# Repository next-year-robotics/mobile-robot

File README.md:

# Mobile Robot

Maknae (Mobile Assistant for Kin's Needs And Errands) is a small mobile robot for older adults who have trouble getting around. The goal is a robot that brings things like a water bottle or glasses at home, walks along with the person outside, and lets family know when something goes wrong.

This repository has the robot itself: the frame CAD and base interface board, the STM32 firmware, and the ROS 2 packages on the Raspberry Pi 5. The phone app and the caregiver dashboard live in their own repositories (see [Related repositories](#related-repositories)).

The base, odometry, person following, the SO-101 arm, the phone link and caregiver telemetry all run on the real robot. LiDAR mapping was added recently, and navigation comes next.

## What it does

- Follows a person carrying an ArUco marker at about 1.1 m, at up to 0.25 m/s, and stops when the marker is lost.
- Picks up objects and hands them over with an SO-101 arm on the top plate.
- Can be driven with a gamepad at any time; `twist_mux` gives it priority over the follower.
- Fuses wheel odometry with the IMU gyro in a `robot_localization` EKF.
- Builds 2D maps with an RPLIDAR C1 and `slam_toolbox`.
- Talks to the phone app over WebSocket: pick a destination, start and stop the trip, and answer SOS requests with the phone's location.
- Sends status, events and SOS to Firebase so a caregiver can watch from the web dashboard and get push notifications.

## Hardware

| Part | Used here |
| --- | --- |
| Frame | Aluminium extrusion, 450 × 400 × 368 mm, 9.8 kg measured |
| Drive | 2 × JGB37-520 DC gear motor with hall encoder, 100 mm wheels, 264 mm track, casters |
| Motor driver | Cytron MDD3A |
| Microcontroller | STM32F446RE (NUCLEO-F446RE), FreeRTOS and micro-ROS |
| Computer | Raspberry Pi 5, Ubuntu 24.04, ROS 2 Jazzy |
| Arm | SO-101 with gripper, USB to the Pi |
| Sensors | Logitech C920 camera, ICM-42688-P IMU (on the MCU, SPI), RPLIDAR C1 |
| Power | 4S LiFePO4 battery with reverse-polarity diode |

The MCU and the Pi are wired directly, STM32 USART1 to Pi UART0 at 921600 baud, and micro-ROS runs over that link. The MCU closes the wheel speed loops and publishes encoders and IMU at 100 Hz. The firmware caps wheel speed at 0.76 m/s; the follow controller stays well below that.

<table>
  <tr>
    <td></td>
    <td></td>
    <td></td>
    <td></td>
  </tr>
  <tr>
    <td align="center">Frame CAD</td>
    <td align="center">Frame</td>
    <td align="center">Base interface board</td>
    <td align="center">Wiring</td>
  </tr>
</table>

## How it fits together

```mermaid
flowchart LR
  APP[Phone app] <-->|WebSocket| BRIDGE
  subgraph PI5["Raspberry Pi 5 (ROS 2 Jazzy)"]
    BRIDGE[mr_phone_bridge] <--> MISSION[mr_mission]
    MISSION --> FOLLOW[follow]
    CAM[C920 camera] --> ARUCO[aruco_opencv] --> TRACK[marker tracker] --> FOLLOW
    FOLLOW --> MUX[twist_mux]
    JOY[Gamepad] --> MUX
    ODOM[mr_base wheel odometry] --> EKF[EKF]
    LIDAR[RPLIDAR C1] --> SLAM[slam_toolbox]
    MISSION --> TELE[mr_care_telemetry]
    ARMCTL[Arm control]
  end
  subgraph MCU["STM32F446RE (FreeRTOS, micro-ROS)"]
    CTRL[Wheel speed control]
    IMU[ICM-42688-P]
  end
  MUX -->|cmd_vel| CTRL
  CTRL -->|encoder ticks| ODOM
  IMU -->|gyro| EKF
  TELE --> RTDB[(Firebase RTDB)] --> DASH[Caregiver dashboard]
  ARMCTL -->|USB| ARM[SO-101 arm]
```

## Repository layout

```text
hardware/mobile_base/      frame CAD (STEP) and measured robot geometry
hardware/base_interface/   KiCad perfboard for the MCU, motor driver, IMU and power
firmware/base_controller/  STM32CubeMX project with FreeRTOS and micro-ROS
software/ros_pkgs/         ROS 2 packages
software/contracts/        JSON schemas shared with the phone app and the dashboard
software/patches/          patches for upstream ROS packages
```

| Package | Purpose |
| --- | --- |
| `mr_description` | URDF from measured geometry, meshes, RViz config |
| `mr_base` | wheel odometry, `odom` to `base_footprint` TF, IMU covariance |
| `mr_bringup` | launch files and config for camera, teleop, `twist_mux`, EKF, LiDAR, SLAM |
| `mr_aruco` | marker tracking filter, person following, alignment to fixed markers |
| `mr_mission` | trip state for the app, turns following on and off, battery estimate |
| `mr_phone_bridge` | WebSocket gateway for the phone app, plus a mock that runs without ROS |
| `mr_care_telemetry` | writes status and events to Firebase RTDB, with an offline queue |
| `mr_msgs`, `mr_aruco_msgs`, `mr_care_msgs` | messages and actions |

## Getting started

### Firmware

The firmware is a CMake project generated by STM32CubeMX. Build the micro-ROS static library once (it runs in Docker), then build and flash with an ST-Link.

```bash
cd firmware/base_controller
./micro_ros/build_libmicroros.sh
cmake --preset Release
cmake --build --preset Release
arm-none-eabi-objcopy -O binary build/Release/base_controller.elf build/Release/base_controller.bin
st-flash --reset write build/Release/base_controller.bin 0x08000000
```

### ROS 2 workspace on the Pi

```bash
mkdir -p ~/ros2_ws/src && cd ~/ros2_ws/src
git clone https://github.com/next-year-robotics/mobile-robot.git
cd ~/ros2_ws
rosdep install --from-paths src --ignore-src -y
colcon build --symlink-install
source install/setup.bash
```

The launch files start `micro_ros_agent` on `/dev/ttyAMA0` from a separate workspace, `~/microros_ws`; build it there following the micro-ROS setup guide. usb_cam 0.8.1 from apt stamps camera frames up to a second in the past, which makes the follower drop every sample. Build usb_cam from source in the same workspace with `software/patches/usb_cam-0.8.1-epoch-time-shift.patch` applied.

### Run

```bash
ros2 launch mr_bringup teleop.launch.py    # drive with the gamepad (hold LB or RB)
ros2 launch mr_bringup follow.launch.py    # follow the marker
ros2 launch mr_bringup slam.launch.py      # drive around slowly and build a map
```

## Roadmap

- Measure the LiDAR mount and tune SLAM
- Nav2 for going to saved places
- Simulation

## Related repositories

- [senior-care-android](https://github.com/next-year-robotics/senior-care-android): phone app for the person going out with the robot
- [senior-care-dashboard](https://github.com/next-year-robotics/senior-care-dashboard): web dashboard for caregivers
- [mobile-robot-booth](https://github.com/next-year-robotics/mobile-robot-booth): live dashboard and avatar used for demos

## License

- `software/` and `firmware/`: [Apache-2.0](LICENSES/Apache-2.0.txt)
- `hardware/`: [CERN-OHL-P-2.0](LICENSES/CERN-OHL-P-2.0.txt)
- Documentation and photos: [CC BY 4.0](LICENSES/CC-BY-4.0.txt)

Third-party code such as the ST HAL, CMSIS and FreeRTOS keeps its own license. See [LICENSE.md](LICENSE.md).

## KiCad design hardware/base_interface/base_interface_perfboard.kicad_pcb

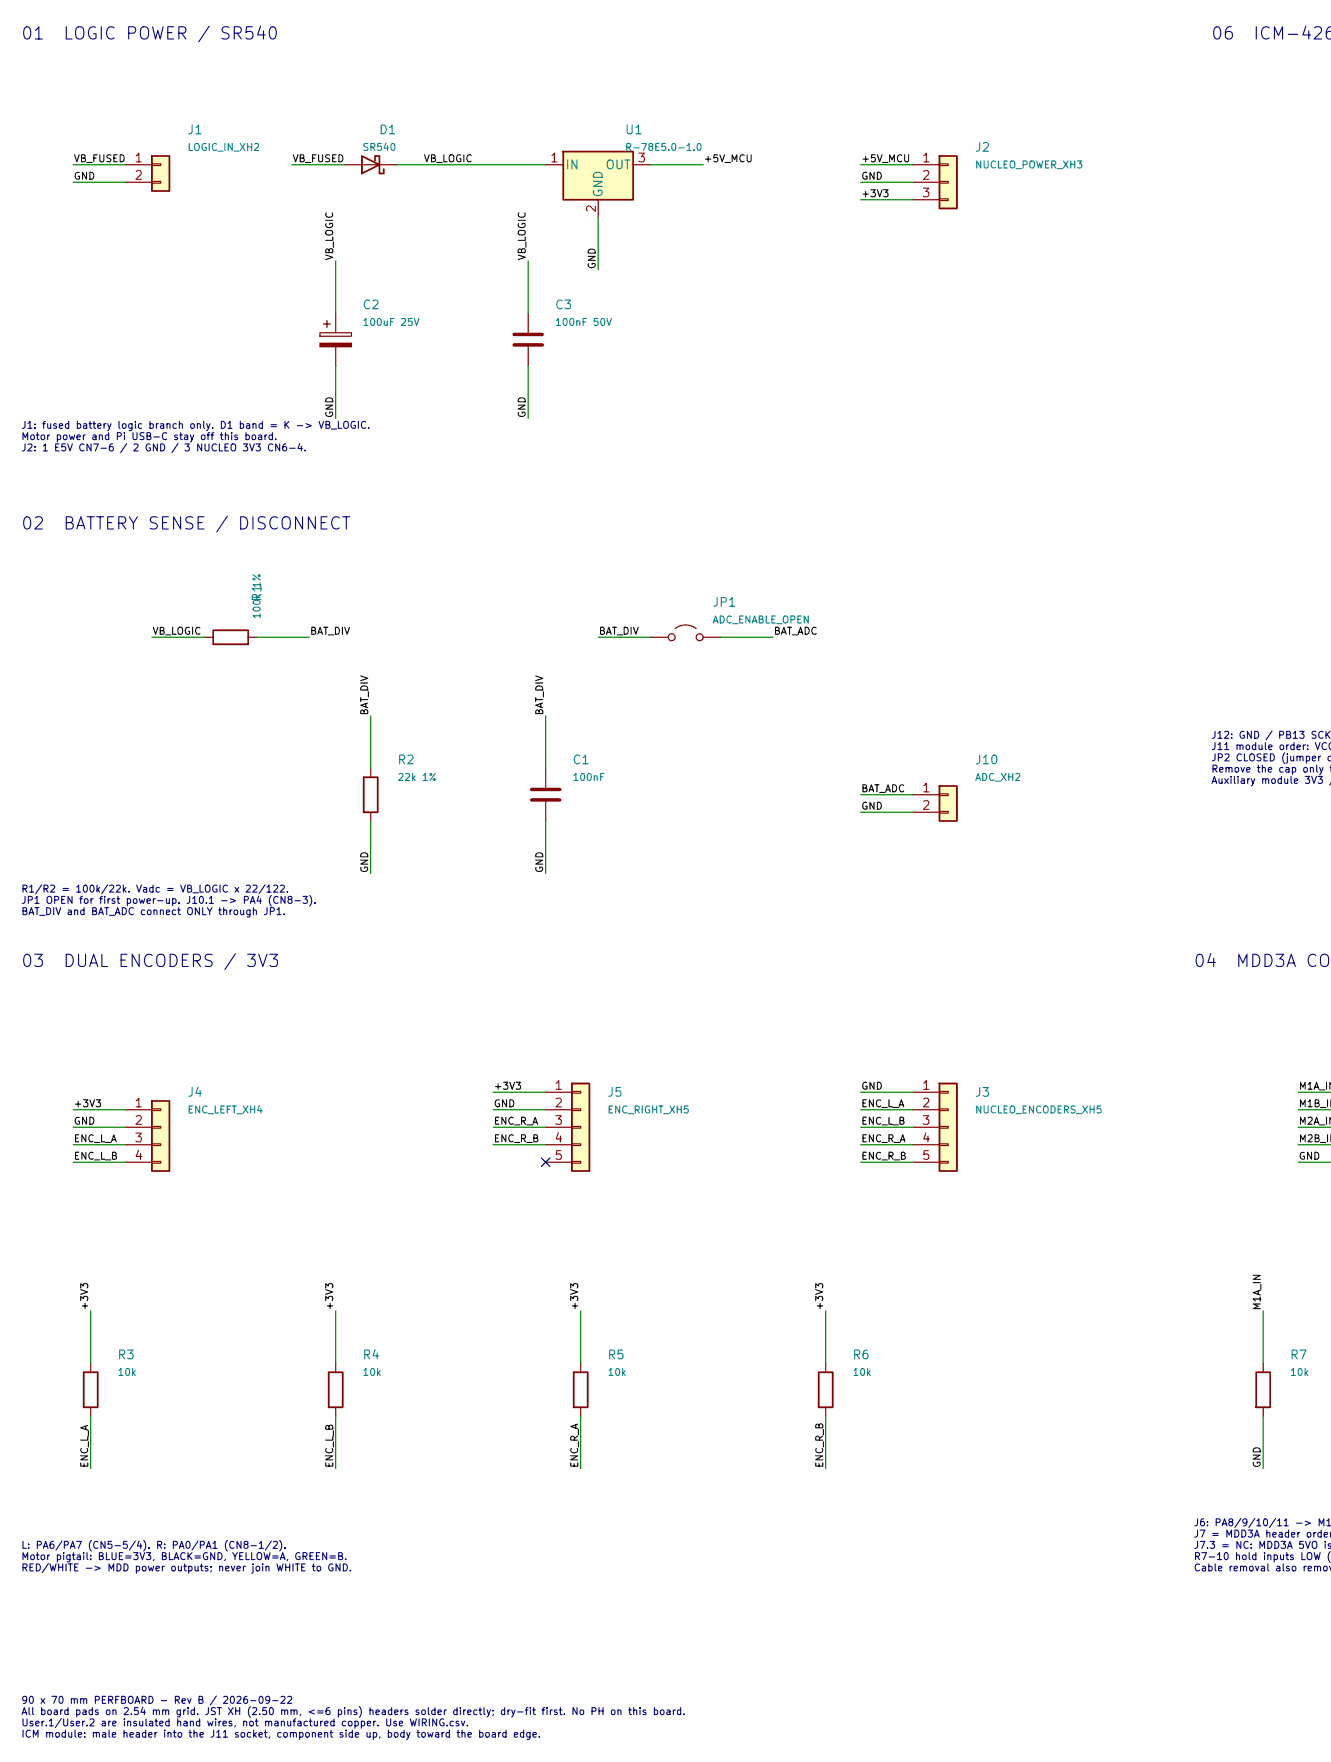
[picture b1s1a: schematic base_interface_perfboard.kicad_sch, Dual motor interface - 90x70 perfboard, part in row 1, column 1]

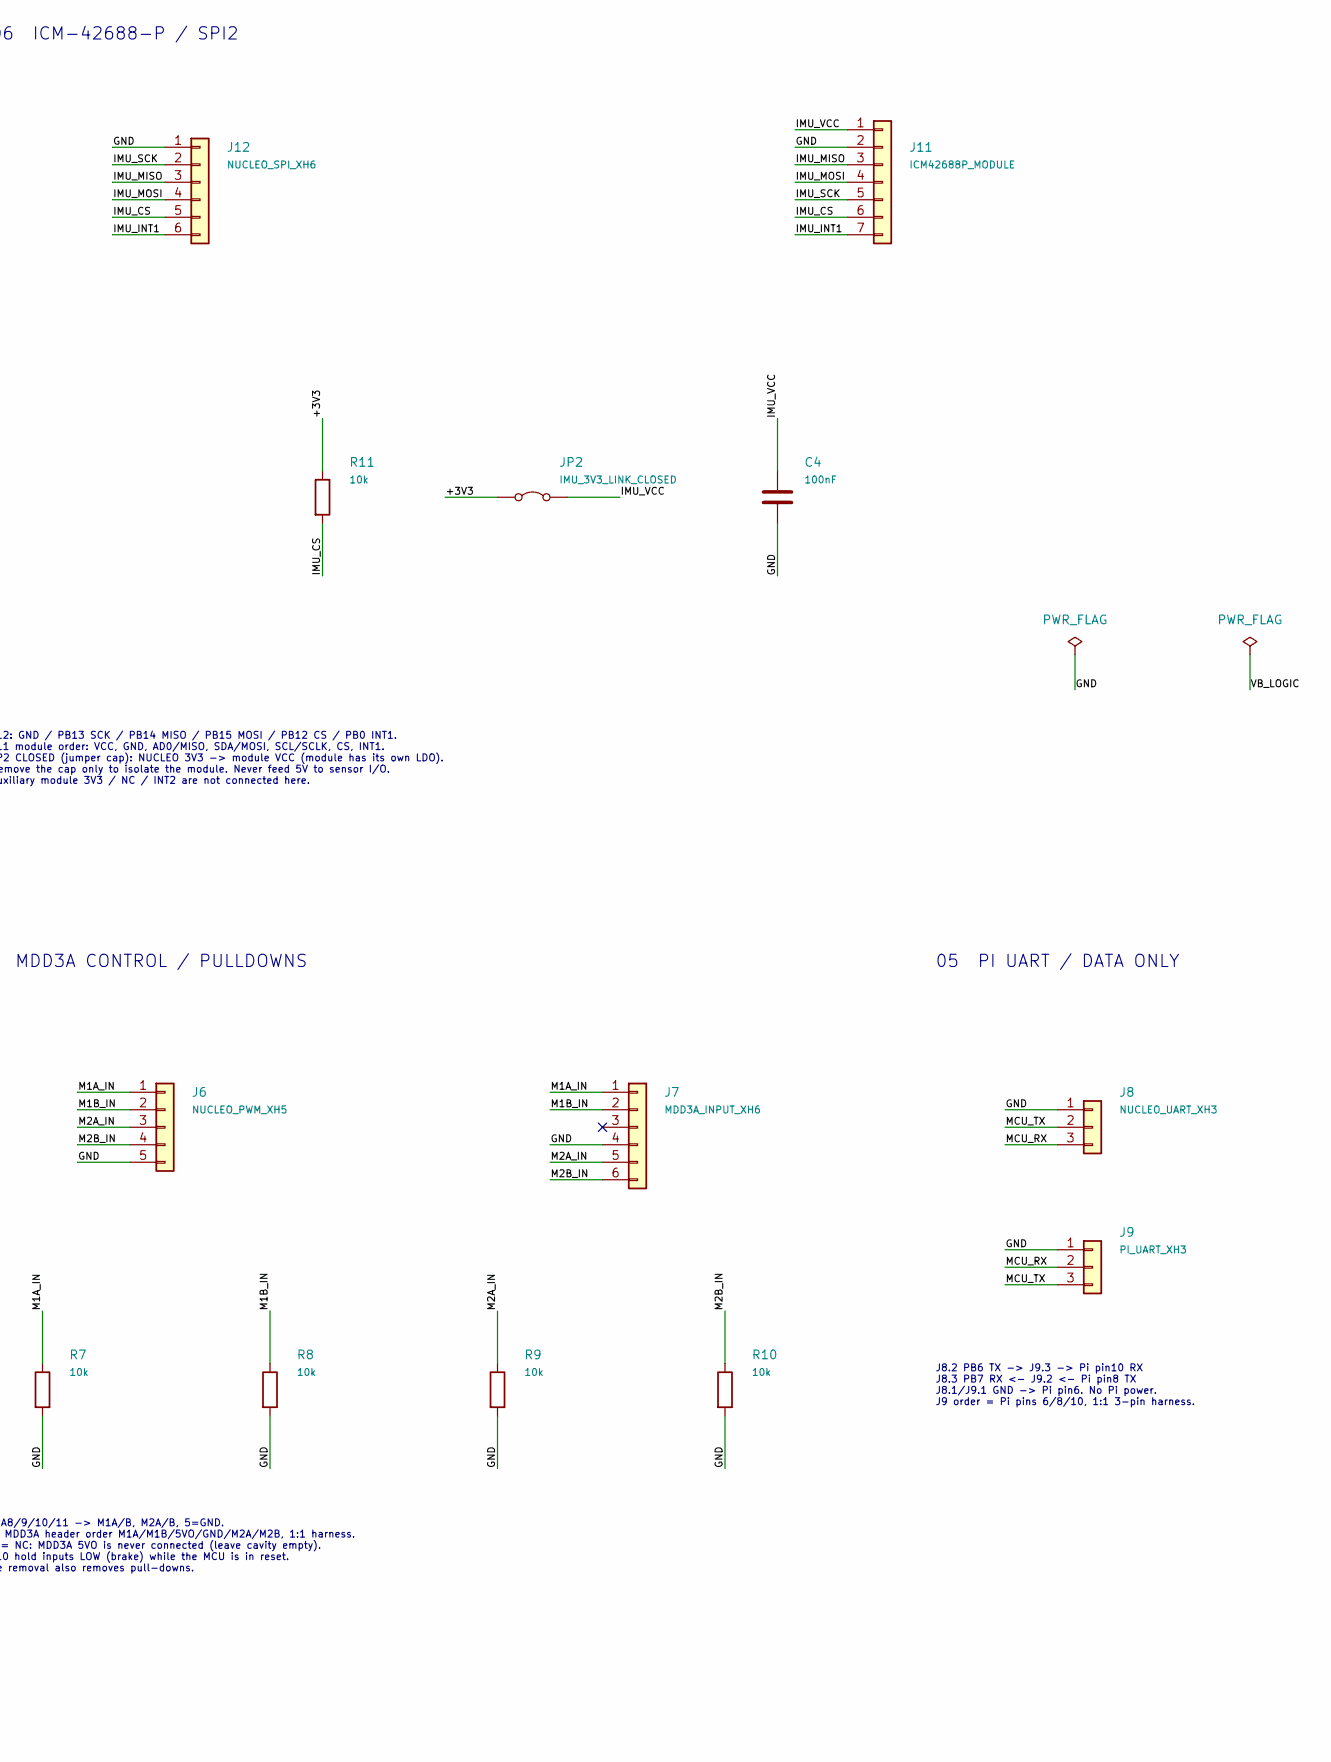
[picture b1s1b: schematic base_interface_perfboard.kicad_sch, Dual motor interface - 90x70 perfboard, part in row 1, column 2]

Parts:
C1: 100nF; C1_Grid
C2: 100uF 25V; C2_Grid
C3: 100nF 50V; C3_Grid
C4: 100nF; C4_Grid
D1: SR540; D1_Grid
J1: LOGIC_IN_XH2; J1_Grid
J2: NUCLEO_POWER_XH3; J2_Grid
J3: NUCLEO_ENCODERS_XH5; J3_Grid
J4: ENC_LEFT_XH4; J4_Grid
J5: ENC_RIGHT_XH5; J5_Grid
J6: NUCLEO_PWM_XH5; J6_Grid
J7: MDD3A_INPUT_XH6; J7_Grid
J8: NUCLEO_UART_XH3; J8_Grid
J9: PI_UART_XH3; J9_Grid
J10: ADC_XH2; J10_Grid
J11: ICM42688P_MODULE; J11_Grid
J12: NUCLEO_SPI_XH6; J12_Grid
JP1: ADC_ENABLE_OPEN; JP1_Grid
JP2: IMU_3V3_LINK_CLOSED; JP2_Grid
R1: 100k 1%; R1_Grid
R2: 22k 1%; R2_Grid
R3: 10k; R3_Grid
R4: 10k; R4_Grid
R5: 10k; R5_Grid
R6: 10k; R6_Grid
R7: 10k; R7_Grid
R8: 10k; R8_Grid
R9: 10k; R9_Grid
R10: 10k; R10_Grid
R11: 10k; R11_Grid
U1: R-78E5.0-1.0; U1_Grid

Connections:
+3V3: J2.3, J4.1, J5.1, JP2.1 (A), R3.1, R4.1, R5.1, R6.1, R11.1
+5V_MCU: J2.1, U1.3 (OUT)
BAT_ADC: J10.1, JP1.2 (B)
BAT_DIV: C1.1, JP1.1 (A), R1.2, R2.1
ENC_L_A: J3.2, J4.3, R3.2
ENC_L_B: J3.3, J4.4, R4.2
ENC_R_A: J3.4, J5.3, R5.2
ENC_R_B: J3.5, J5.4, R6.2
GND: C1.2, C2.2, C3.2, C4.2, J1.2, J2.2, J3.1, J4.2, J5.2, J6.5, J7.4, J8.1, J9.1, J10.2, J11.2, J12.1, R2.2, R7.2, R8.2, R9.2, R10.2, U1.2 (GND)
IMU_CS: J11.6, J12.5, R11.2
IMU_INT1: J11.7, J12.6
IMU_MISO: J11.3, J12.3
IMU_MOSI: J11.4, J12.4
IMU_SCK: J11.5, J12.2
IMU_VCC: C4.1, J11.1, JP2.2 (B)
M1A_IN: J6.1, J7.1, R7.1
M1B_IN: J6.2, J7.2, R8.1
M2A_IN: J6.3, J7.5, R9.1
M2B_IN: J6.4, J7.6, R10.1
MCU_RX: J8.3, J9.2
MCU_TX: J8.2, J9.3
VB_FUSED: D1.2 (A), J1.1
VB_LOGIC: C2.1, C3.1, D1.1 (K), R1.1, U1.1 (IN)

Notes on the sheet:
01 LOGIC POWER / SR540
02 BATTERY SENSE / DISCONNECT
03 DUAL ENCODERS / 3V3
04 MDD3A CONTROL / PULLDOWNS
05 PI UART / DATA ONLY
06 ICM-42688-P / SPI2
J1: fused battery logic branch only. D1 band = K -> VB_LOGIC. Motor power and Pi USB-C stay off this board. J2: 1 E5V CN7-6 / 2 GND / 3 NUCLEO 3V3 CN6-4.
R1/R2 = 100k/22k. Vadc = VB_LOGIC x 22/122. JP1 OPEN for first power-up. J10.1 -> PA4 (CN8-3). BAT_DIV and BAT_ADC connect ONLY through JP1.
L: PA6/PA7 (CN5-5/4). R: PA0/PA1 (CN8-1/2). Motor pigtail: BLUE=3V3, BLACK=GND, YELLOW=A, GREEN=B. RED/WHITE -> MDD power outputs; never join WHITE to GND.
J6: PA8/9/10/11 -> M1A/B, M2A/B, 5=GND. J7 = MDD3A header order M1A/M1B/5VO/GND/M2A/M2B, 1:1 harness. J7.3 = NC: MDD3A 5VO is never connected (leave cavity empty). R7-10 hold inputs LOW (brake) while the MCU is in reset. Cable removal also removes pull-downs.
J8.2 PB6 TX -> J9.3 -> Pi pin10 RX J8.3 PB7 RX <- J9.2 <- Pi pin8 TX J8.1/J9.1 GND -> Pi pin6. No Pi power. J9 order = Pi pins 6/8/10, 1:1 3-pin harness.
J12: GND / PB13 SCK / PB14 MISO / PB15 MOSI / PB12 CS / PB0 INT1. J11 module order: VCC, GND, AD0/MISO, SDA/MOSI, SCL/SCLK, CS, INT1. JP2 CLOSED (jumper cap): NUCLEO 3V3 -> module VCC (module has its own LDO). Remove the cap only to isolate the module. Never feed 5V to sensor I/O. Auxiliary module 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
90 x 70 mm PERFBOARD - Rev B / 2026-09-22 All board pads on 2.54 mm grid. JST XH (2.50 mm, <=6 pins) headers solder directly; dry-fit first. No PH on this board. User.1/User.2 are insulated hand wires, not manufactured copper. Use WIRING.csv. ICM module: male header into the J11 socket, component s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

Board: 2 copper layers, 31 parts (0 on the bottom side), 23 nets, no tracks yet.

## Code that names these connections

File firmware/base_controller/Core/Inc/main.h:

/* USER CODE BEGIN Header */
/**
  ******************************************************************************
  * @file           : main.h
  * @brief          : Header for main.c file.
  *                   This file contains the common defines of the application.
  ******************************************************************************
  * @attention
  *
  * Copyright (c) 2026 STMicroelectronics.
  * All rights reserved.
  *
  * This software is licensed under terms that can be found in the LICENSE file
  * in the root directory of this software component.
  * If no LICENSE file comes with this software, it is provided AS-IS.
  *
  ******************************************************************************
  */
/* USER CODE END Header */

/* Define to prevent recursive inclusion -------------------------------------*/
#ifndef __MAIN_H
#define __MAIN_H

#ifdef __cplusplus
extern "C" {
#endif

/* Includes ------------------------------------------------------------------*/
#include "stm32f4xx_hal.h"

/* Private includes ----------------------------------------------------------*/
/* USER CODE BEGIN Includes */

/* USER CODE END Includes */

/* Exported types ------------------------------------------------------------*/
/* USER CODE BEGIN ET */

/* USER CODE END ET */

/* Exported constants --------------------------------------------------------*/
/* USER CODE BEGIN EC */

/* USER CODE END EC */

/* Exported macro ------------------------------------------------------------*/
/* USER CODE BEGIN EM */

/* USER CODE END EM */

/* Exported functions prototypes ---------------------------------------------*/
void Error_Handler(void);

/* USER CODE BEGIN EFP */

/* USER CODE END EFP */

/* Private defines -----------------------------------------------------------*/
#define B1_Pin GPIO_PIN_13
#define B1_GPIO_Port GPIOC
#define USART_TX_Pin GPIO_PIN_2
#define USART_TX_GPIO_Port GPIOA
#define USART_RX_Pin GPIO_PIN_3
#define USART_RX_GPIO_Port GPIOA
#define BAT_ADC_Pin GPIO_PIN_4
#define BAT_ADC_GPIO_Port GPIOA
#define LD2_Pin GPIO_PIN_5
#define LD2_GPIO_Port GPIOA
#define IMU_INT1_Pin GPIO_PIN_0
#define IMU_INT1_GPIO_Port GPIOB
#define IMU_INT1_EXTI_IRQn EXTI0_IRQn
#define IMU_CS_Pin GPIO_PIN_12
#define IMU_CS_GPIO_Port GPIOB
#define TMS_Pin GPIO_PIN_13
#define TMS_GPIO_Port GPIOA
#define TCK_Pin GPIO_PIN_14
#define TCK_GPIO_Port GPIOA
#define SWO_Pin GPIO_PIN_3
#define SWO_GPIO_Port GPIOB

/* USER CODE BEGIN Private defines */

/* USER CODE END Private defines */

#ifdef __cplusplus
}
#endif

#endif /* __MAIN_H */
